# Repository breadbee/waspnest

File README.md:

# Waspnest

This might be something for makefaire tokyo 2020..

```
     ------   -------                                                                         -------
    | RJ45 | | usb-c |                                                                       | usb-c |
     ------   -------                                                                         -------
       |         |                                                                               |
       |    ----------                                                                        --------
       |   | upstream |                                                                      | IP2721 | 
       |   |          |                                                                       --------
       |   |  USB2517 |
       |   |          |   --------
       |   |    port1 |--| ch340e |-----\
       |   |          |   --------      |
       |   |    port2 |--| ch340e |-----|---------\
       |   |          |   --------      |         |
       |   |    port3 |--| ch340e |-----|---------|---------\
       |   |          |   --------      |         |         |
       |   |    port4 |--| ch340e |-----|---------|---------|---------\
       |   |          |   --------      |         |         |         |
       |   |    port5 |--| ch340e |-----|---------|---------|---------|---------\
       |   |          |   --------      |         |         |         |         |
       |   |    port6 |--| ch340e |-----|---------|---------|---------|---------|---------\
       |   |          |   --------      |         |         |         |         |         |
       |   |    port7 |--| ch340e |-----|---------|---------|---------|---------|---------|----------\
       |    ---------     --------      |         |         |         |         |         |          |
       |                                |         |         |         |         |         |          |                      
  ------------                          |         |         |         |         |         |          |
 |   port 0   |                         |         |         |         |         |         |          |
 |            |                         |         |         |         |         |         |          |
 |  RTL8309N  |                         |         |         |         |         |         |          |
 |            |                     ---------     |         |         |         |         |          |
 |      port1 |--------------------| drone 1 |    |         |         |         |         |          |
 |            |                     --------- ---------     |         |         |         |          |
 |      port2 |------------------------------| drone 2 |    |         |         |         |          |
 |            |                               --------- ---------     |         |         |          |
 |      port3 |----------------------------------------| drone 3 |    |         |         |          |
 |            |                                         --------- ---------     |         |          |
 |      port4 |--------------------------------------------------| drone 4 |    |         |          |
 |            |                                                   --------- ---------     |          |
 |      port5 |------------------------------------------------------------| drone 5 |    |          |
 |            |                                                             --------- ---------      |
 |      port6 |----------------------------------------------------------------------| drone 6 |     |
 |            |                                                                       --------- ------------
 |      port7 |--------------------------------------------------------------------------------| Supervisor |
  ------------                                                                                  ------------

```

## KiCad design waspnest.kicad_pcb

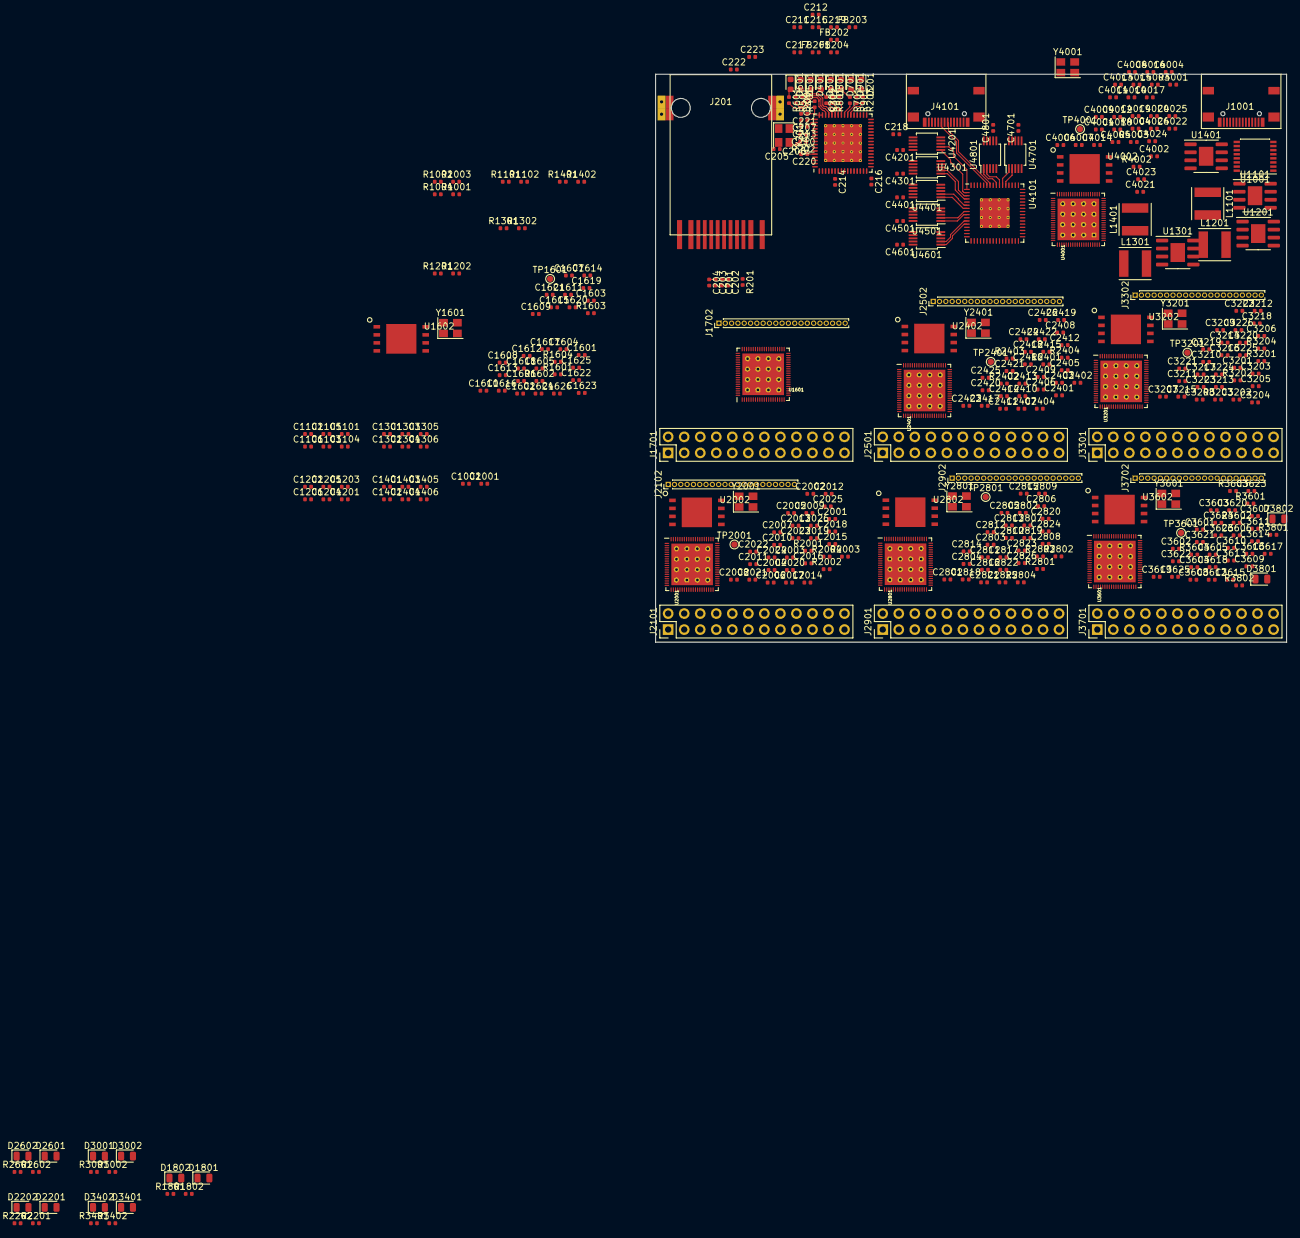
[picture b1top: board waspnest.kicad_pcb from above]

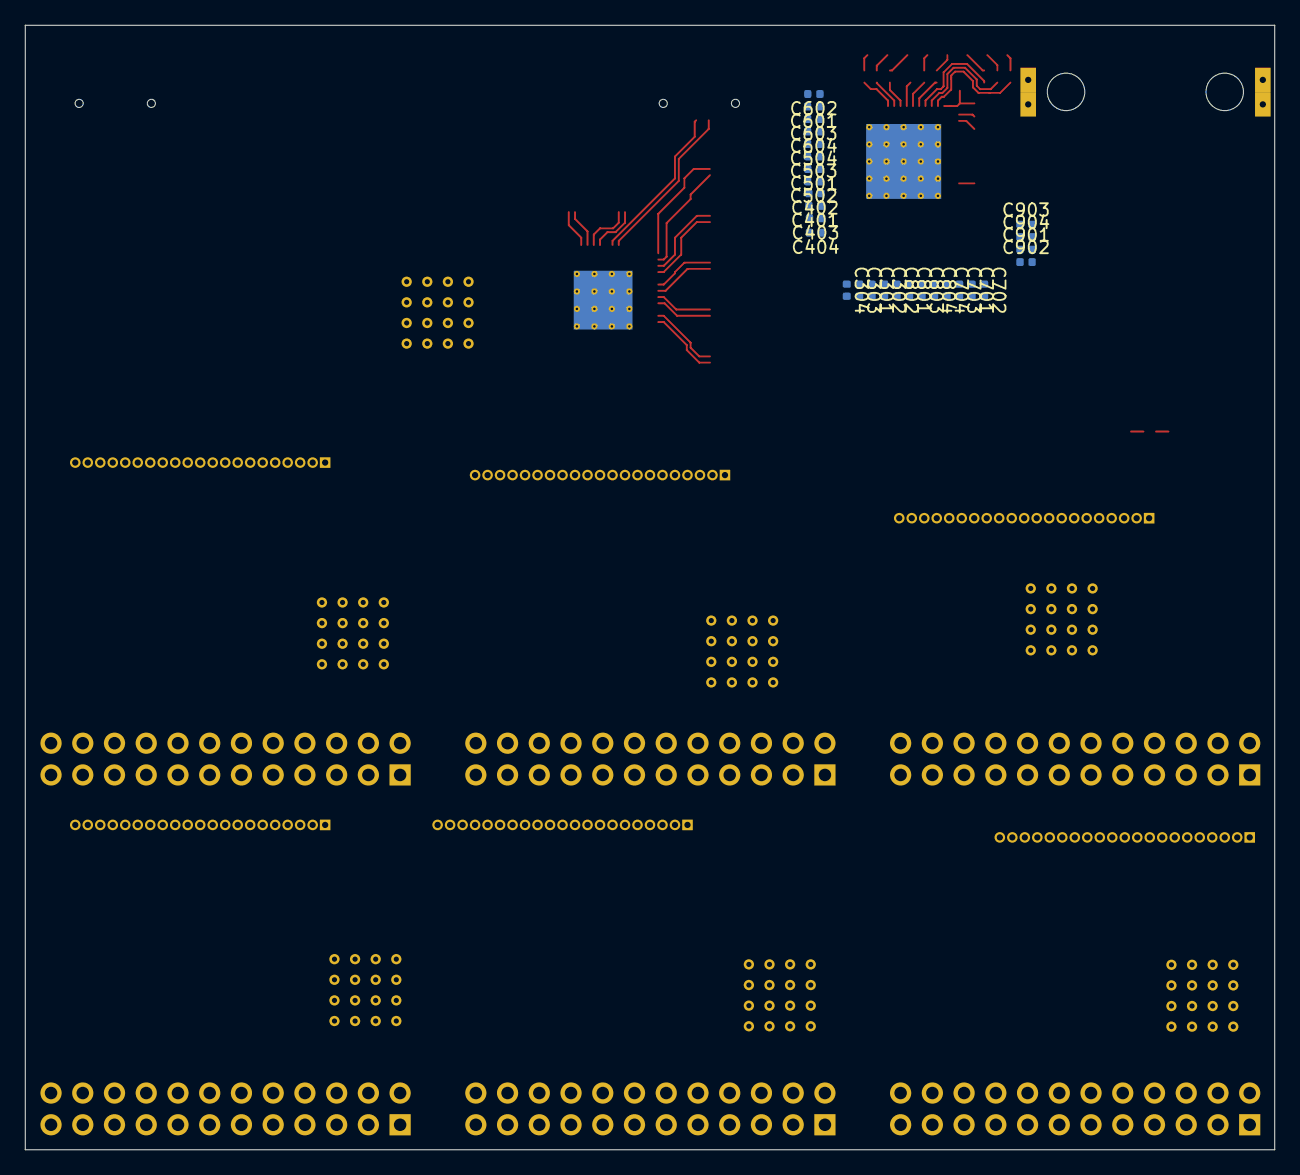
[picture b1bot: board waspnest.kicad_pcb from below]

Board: 4 copper layers, 100.0 x 90.0 mm, 414 parts (28 on the bottom side), 473 nets.

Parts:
C201, C202, C203, C204, C205, C206, C207, C208, C209, C210, C211, C212, C213, C214, C215, C216, C217, C218, C219, C220, C221, C222, C223, C301, C302, C303, C304, C401, C402, C403, C404, C501, C502, C503, C504, C601, C602, C603, C604, C701, C702, C703, C704, C801, C802, C803, C804, C901, C902, C903, C904, C1001, C1002, C1101, C1102, C1103, C1104, C1105, C1106, C1201, C1202, C1203, C1204, C1205, C1206, C1301, C1302, C1303, C1304, C1305, C1306, C1401, C1402, C1403, C1404, C1405, C1406: C; C_0402_1005Metric
C1601, C1602, C1603, C1604, C1605, C1606, C1607, C1608, C1609, C1610, C1611, C1612, C1613, C1614, C1618, C1619, C1621, C1622, C1624, C1626, C2001, C2002, C2003, C2004, C2005, C2006, C2007, C2008, C2009, C2010, C2011, C2012, C2013, C2014, C2018, C2019, C2021, C2022, C2024, C2026, C2401, C2402, C2403, C2404, C2405, C2406, C2407, C2408, C2409, C2410, C2411, C2412, C2413, C2414, C2418, C2419, C2421, C2422, C2424, C2426, C2801, C2802, C2803, C2804, C2805, C2806, C2807, C2808, C2809, C2810, C2811, C2812, C2813, C2814, C2818, C2819, C2821, C2822, C2824, C2826, C3201, C3202, C3203, C3204, C3205, C3206, C3207, C3208, C3209, C3210, C3211, C3212, C3213, C3214, C3218, C3219, C3221, C3222, C3224, C3226, C3601, C3602, C3603, C3604, C3605, C3606, C3607, C3608, C3609, C3610, C3611, C3612, C3613, C3614, C3618, C3619, C3621, C3622, C3624, C3626, C4001, C4002, C4003, C4004, C4005, C4006, C4007, C4008, C4009, C4010, C4011, C4012, C4013, C4014, C4018, C4019, C4021, C4022, C4024, C4026, C4201, C4301, C4401, C4501, C4601, C4701, C4801: 1uf; C_0402_1005Metric
C1615, C1616, C1617, C2015, C2016, C2017, C2415, C2416, C2417, C2815, C2816, C2817, C3215, C3216, C3217, C3615, C3616, C3617, C4015, C4016, C4017: 10uf; C_0402_1005Metric
C1620, C2020, C2420, C2820, C3220, C3620, C4020: 1uF; C_0402_1005Metric
C1623, C1625, C2023, C2025, C2423, C2425, C2823, C2825, C3223, C3225, C3623, C3625, C4023, C4025: 18pf; C_0402_1005Metric
D201, D301, D401, D501, D601, D701, D801, D901: LED; LED_0603_1608Metric
D1801, D1802, D2201, D2202, D2601, D2602, D3001, D3002, D3401, D3402, D3801, D3802: LED_Small; LED_0805_2012Metric
FB201, FB202, FB203, FB204: Ferrite_Bead; L_0402_1005Metric
J201: HR961160C
J1001, J4101: usbc-16p; usbc16p
J1701, J2101, J2501, J2901, J3301, J3701: Conn_02x12_Odd_Even; PinHeader_2x12_P2.54mm_Vertical
J1702, J2102, J2502, J2902, J3302, J3702: Conn_01x21; PinHeader_1x21_P1.00mm_Vertical
L1101, L1201, L1301, L1401: L; L_Taiyo-Yuden_NR-50xx
R201, R203, R301, R401, R501, R601, R701, R801, R901, R1002, R1003, R1004, R1101, R1102, R1201, R1202, R1301, R1302, R1401, R1402: R; R_0402_1005Metric
R202: 2.49K 1%; R_0402_1005Metric
R1001: 100k; R_0402_1005Metric
R1601, R1602, R2001, R2002, R2401, R2402, R2801, R2802, R3201, R3202, R3601, R3602, R4001, R4002: 0; R_0402_1005Metric
R1603, R2003, R2403, R2803, R3203, R3603, R4003: 1.2m; R_0402_1005Metric
R1604, R2004, R2404, R2804, R3204, R3604, R4004: 1m; R_0402_1005Metric
R1801, R1802, R2201, R2202, R2601, R2602, R3001, R3002, R3401, R3402, R3801, R3802: 390; R_0402_1005Metric
TP1601, TP2001, TP2401, TP2801, TP3201, TP3601, TP4001: TestPoint; TestPoint_Pad_D1.0mm
U201: RTL8309N; QFN-64-1EP_9x9mm_P0.5mm_EP6x6mm_ThermalVias
U1001: IP2721; SSOP-16_4.4x5.2mm_P0.65mm
U1101, U1201, U1301, U1401: SY8205FCC; SOIC-8-1EP_3.9x4.9mm_P1.27mm_EP2.29x3mm
U1601, U2001, U2401, U2801, U3201, U3601, U4001: msc313e; QFN-80_EP_8x8_Pitch0.35mm
U1602, U2002, U2402, U2802, U3202, U3602, U4002: spinor; wson8-8x6mm
U4101: USB2517; QFN-64-1EP_9x9mm_P0.5mm_EP4.7x4.7mm_ThermalVias
U4201, U4301, U4401, U4501, U4601, U4701, U4801: ch340e; MSOP-10_3x3mm_P0.5mm
Y201: 25MHz; Crystal_SMD_Abracon_ABM8G-4Pin_3.2x2.5mm
Y1601, Y2001, Y2401, Y2801, Y3201, Y3601, Y4001: Crystal_GND24; Crystal_SMD_Abracon_ABM8G-4Pin_3.2x2.5mm

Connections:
+1V0: C1405.1, C1406.1, C1603.1, C1605.1, C1606.1, C1607.1, C1608.1, C1610.1, C2003.1, C2005.1, C2006.1, C2007.1, C2008.1, C2010.1, C2403.1, C2405.1, C2406.1, C2407.1, C2408.1, C2410.1, C2803.1, C2805.1, C2806.1, C2807.1, C2808.1, C2810.1, C3203.1, C3205.1, C3206.1, C3207.1, C3208.1, C3210.1, C3603.1, C3605.1, C3606.1, C3607.1, C3608.1, C3610.1, C4003.1, C4005.1, C4006.1, C4007.1, C4008.1, C4010.1, L1401.2, R1402.1, U1601.5, U1601.8, U1601.40, U1601.60, U1601.61, U1601.67, U2001.5, U2001.8, U2001.40, U2001.60, U2001.61, U2001.67, U2401.5, U2401.8, U2401.40, U2401.60, U2401.61, U2401.67, U2801.5, U2801.8, U2801.40, U2801.60, U2801.61, U2801.67, U3201.5, U3201.8, U3201.40, U3201.60, U3201.61, U3201.67, U3601.5, U3601.8, U3601.40, U3601.60, U3601.61, U3601.67, U4001.5, U4001.8, U4001.40, U4001.60, U4001.61, U4001.67
+1V8: C1305.1, C1306.1, C1611.1, C1612.1, C1613.1, C2011.1, C2012.1, C2013.1, C2411.1, C2412.1, C2413.1, C2811.1, C2812.1, C2813.1, C3211.1, C3212.1, C3213.1, C3611.1, C3612.1, C3613.1, C4011.1, C4012.1, C4013.1, L1301.2, R1302.1, U1601.3, U1601.4, U1601.6, U2001.3, U2001.4, U2001.6, U2401.3, U2401.4, U2401.6, U2801.3, U2801.4, U2801.6, U3201.3, U3201.4, U3201.6, U3601.3, U3601.4, U3601.6, U4001.3, U4001.4, U4001.6
+3V3: C207.1, C209.1, C1205.1, C1206.1, C1609.1, C1618.1, C1619.1, C1620.1, C1621.1, C1622.1, C1624.1, C1626.1, C2009.1, C2018.1, C2019.1, C2020.1, C2021.1, C2022.1, C2024.1, C2026.1, C2409.1, C2418.1, C2419.1, C2420.1, C2421.1, C2422.1, C2424.1, C2426.1, C2809.1, C2818.1, C2819.1, C2820.1, C2821.1, C2822.1, C2824.1, C2826.1, C3209.1, C3218.1, C3219.1, C3220.1, C3221.1, C3222.1, C3224.1, C3226.1, C3609.1, C3618.1, C3619.1, C3620.1, C3621.1, C3622.1, C3624.1, C3626.1, C4009.1, C4018.1, C4019.1, C4020.1, C4021.1, C4022.1, C4024.1, C4026.1, C4201.1, C4301.1, C4401.1, C4501.1, C4601.1, C4701.1, C4801.1, FB203.2, FB204.2, J1701.2, J1702.1, J2101.2, J2102.1, J2501.2, J2502.1, J2901.2, J2902.1, J3301.2, J3302.1, J3701.2, J3702.1, L1201.2, R1202.1, R1601.1, R1602.1, R2001.1, R2002.1, R2401.1, R2402.1, R2801.1, R2802.1, R3201.1, R3202.1, R3601.1, R3602.1, R4001.1, R4002.1, U201.41, U201.49, U1601.7, U1601.14, U1601.27, U1601.35, U1601.43, U1601.62, U1602.7, U1602.8, U2001.7, U2001.14, U2001.27, U2001.35, U2001.43, U2001.62, U2002.7, U2002.8, U2401.7, U2401.14, U2401.27, U2401.35, U2401.43, U2401.62, U2402.7, U2402.8, U2801.7, U2801.14, U2801.27, U2801.35, U2801.43, U2801.62, U2802.7, U2802.8, U3201.7, U3201.14, U3201.27, U3201.35, U3201.43, U3201.62, U3202.7, U3202.8, U3601.7, U3601.14, U3601.27, U3601.35, U3601.43, U3601.62, U3602.7, U3602.8, U4001.7, U4001.14, U4001.27, U4001.35, U4001.43, U4001.62, U4002.7, U4002.8, U4201.7, U4201.10, U4301.7, U4301.10, U4401.7, U4401.10, U4501.7, U4501.10, U4601.7, U4601.10, U4701.7, U4701.10, U4801.7, U4801.10
+5V: C1105.1, C1106.1, C1614.1, C1615.1, C1616.1, C1617.1, C2014.1, C2015.1, C2016.1, C2017.1, C2414.1, C2415.1, C2416.1, C2417.1, C2814.1, C2815.1, C2816.1, C2817.1, C3214.1, C3215.1, C3216.1, C3217.1, C3614.1, C3615.1, C3616.1, C3617.1, C4014.1, C4015.1, C4016.1, C4017.1, J1701.1, J1702.10, J2101.1, J2102.10, J2501.1, J2502.10, J2901.1, J2902.10, J3301.1, J3302.10, J3701.1, J3702.10, L1101.2, R1102.1
+12V: C1002.1, C1103.2, C1203.2, C1303.2, C1403.2, J1001.a4, J1001.a9, J1001.b4, J1001.b9, R1001.1, U1001.2, U1001.16, U1101.7, U1101.8, U1201.7, U1201.8, U1301.7, U1301.8, U1401.7, U1401.8
/consoles/console_drone0/usb_dn: U4101.3, U4301.2
/consoles/console_drone0/usb_dp: U4101.4, U4301.1
/consoles/console_drone1/usb_dn: U4101.6, U4401.2
/consoles/console_drone1/usb_dp: U4101.7, U4401.1
/consoles/console_drone2/usb_dn: U4101.8, U4501.2
/consoles/console_drone2/usb_dp: U4101.9, U4501.1
/consoles/console_drone3/usb_dn: U4101.11, U4601.2
/consoles/console_drone3/usb_dp: U4101.12, U4601.1
/consoles/console_drone4/usb_dn: U4101.53, U4701.2
/consoles/console_drone4/usb_dp: U4101.54, U4701.1
/consoles/console_drone5/usb_dn: U4101.55, U4801.2
/consoles/console_drone5/usb_dp: U4101.56, U4801.1
/consoles/console_queen/usb_dn: U4101.1, U4201.2
/consoles/console_queen/usb_dp: U4101.2, U4201.1
/drone0/drone_core/fuart_cts: J1701.17, U1601.38
/drone0/drone_core/fuart_rts: J1701.18, U1601.39
/drone0/drone_core/fuart_rx: J1701.15, U1601.36
/drone0/drone_core/fuart_tx: J1701.16, U1601.37
/drone0/drone_core/i2c1_scl: J1701.5, U1601.41
/drone0/drone_core/i2c1_sda: J1701.6, U1601.42
/drone0/drone_core/pm_gpio4: J1701.4, U1601.21
/drone0/drone_core/pm_sd_cdz: J1702.8, U1601.15
/drone0/drone_core/reset: C1609.2, R1603.1, U1601.17
/drone0/drone_core/sar_gpio0: J1701.14, U1601.12
/drone0/drone_core/sar_gpio1: J1701.13, U1601.11
/drone0/drone_core/sar_gpio2: J1701.11, U1601.10
/drone0/drone_core/sar_gpio3: J1701.12, U1601.9
/drone0/drone_core/sd_clk: J1702.7, U1601.68
/drone0/drone_core/sd_cmd: J1702.6, U1601.69
/drone0/drone_core/sd_d0: J1702.5, U1601.70
/drone0/drone_core/sd_d1: J1702.4, U1601.71
/drone0/drone_core/sd_d2: J1702.3, U1601.72
/drone0/drone_core/sd_d3: J1702.2, U1601.73
/drone0/drone_core/spi0_ck: J1701.8, U1601.64
/drone0/drone_core/spi0_cz: J1701.7, U1601.63
/drone0/drone_core/spi0_di: J1701.9, U1601.65
/drone0/drone_core/spi0_do: J1701.10, U1601.66
/drone0/drone_core/spinor_miso: U1601.25, U1602.2
/drone0/drone_core/spinor_mosi: U1601.23, U1602.5
/drone0/drone_core/spinor_sck: U1601.26, U1602.6
/drone0/drone_core/spinor_~cs: U1601.22, U1602.1
/drone0/drone_core/spinor_~wp: U1601.24, U1602.3
/drone0/drone_core/sr_io2: J1701.24, U1601.44
/drone0/drone_core/sr_io3: J1701.23, U1601.45
/drone0/drone_core/sr_io4: J1701.22, U1601.46
/drone0/drone_core/sr_io5: J1701.21, U1601.47
/drone0/drone_core/sr_io6: J1701.20, U1601.48
/drone0/drone_core/sr_io7: J1701.19, U1601.49
/drone0/drone_core/sr_io8: J1702.21, U1601.50
/drone0/drone_core/sr_io9: J1702.20, U1601.51
/drone0/drone_core/sr_io10: J1702.19, U1601.52
/drone0/drone_core/sr_io11: J1702.18, U1601.53
/drone0/drone_core/sr_io12: J1702.17, U1601.54
/drone0/drone_core/sr_io13: J1702.16, U1601.55
/drone0/drone_core/sr_io14: J1702.15, U1601.56
/drone0/drone_core/sr_io15: J1702.14, U1601.57
/drone0/drone_core/usb_dm: J1702.11, U1601.75
/drone0/drone_core/usb_dp: J1702.12, U1601.76
/drone0/drone_core/xtal_in: C1623.1, R1604.2, U1601.28, Y1601.1
/drone0/drone_core/xtal_out: C1625.1, R1604.1, U1601.29, Y1601.3
/drone0/drone_leds/led0: R1801.1, U1601.58
/drone0/drone_leds/led1: R1802.1, U1601.59
/drone1/drone_core/fuart_cts: J2101.17, U2001.38
/drone1/drone_core/fuart_rts: J2101.18, U2001.39
/drone1/drone_core/fuart_rx: J2101.15, U2001.36
/drone1/drone_core/fuart_tx: J2101.16, U2001.37
/drone1/drone_core/i2c1_scl: J2101.5, U2001.41
/drone1/drone_core/i2c1_sda: J2101.6, U2001.42
/drone1/drone_core/pm_gpio4: J2101.4, U2001.21
/drone1/drone_core/pm_sd_cdz: J2102.8, U2001.15
/drone1/drone_core/reset: C2009.2, R2003.1, U2001.17
/drone1/drone_core/sar_gpio0: J2101.14, U2001.12
/drone1/drone_core/sar_gpio1: J2101.13, U2001.11
/drone1/drone_core/sar_gpio2: J2101.11, U2001.10
/drone1/drone_core/sar_gpio3: J2101.12, U2001.9
/drone1/drone_core/sd_clk: J2102.7, U2001.68
/drone1/drone_core/sd_cmd: J2102.6, U2001.69
/drone1/drone_core/sd_d0: J2102.5, U2001.70
/drone1/drone_core/sd_d1: J2102.4, U2001.71
/drone1/drone_core/sd_d2: J2102.3, U2001.72
/drone1/drone_core/sd_d3: J2102.2, U2001.73
/drone1/drone_core/spi0_ck: J2101.8, U2001.64
/drone1/drone_core/spi0_cz: J2101.7, U2001.63
/drone1/drone_core/spi0_di: J2101.9, U2001.65
/drone1/drone_core/spi0_do: J2101.10, U2001.66
/drone1/drone_core/spinor_miso: U2001.25, U2002.2
/drone1/drone_core/spinor_mosi: U2001.23, U2002.5
/drone1/drone_core/spinor_sck: U2001.26, U2002.6
/drone1/drone_core/spinor_~cs: U2001.22, U2002.1
/drone1/drone_core/spinor_~wp: U2001.24, U2002.3
/drone1/drone_core/sr_io2: J2101.24, U2001.44
/drone1/drone_core/sr_io3: J2101.23, U2001.45
/drone1/drone_core/sr_io4: J2101.22, U2001.46
/drone1/drone_core/sr_io5: J2101.21, U2001.47
/drone1/drone_core/sr_io6: J2101.20, U2001.48
/drone1/drone_core/sr_io7: J2101.19, U2001.49
/drone1/drone_core/sr_io8: J2102.21, U2001.50
/drone1/drone_core/sr_io9: J2102.20, U2001.51
/drone1/drone_core/sr_io10: J2102.19, U2001.52
/drone1/drone_core/sr_io11: J2102.18, U2001.53
/drone1/drone_core/sr_io12: J2102.17, U2001.54
/drone1/drone_core/sr_io13: J2102.16, U2001.55
/drone1/drone_core/sr_io14: J2102.15, U2001.56
/drone1/drone_core/sr_io15: J2102.14, U2001.57
/drone1/drone_core/usb_dm: J2102.11, U2001.75
/drone1/drone_core/usb_dp: J2102.12, U2001.76
/drone1/drone_core/xtal_in: C2023.1, R2004.2, U2001.28, Y2001.1
/drone1/drone_core/xtal_out: C2025.1, R2004.1, U2001.29, Y2001.3
/drone1/drone_leds/led0: R2201.1, U2001.58
/drone1/drone_leds/led1: R2202.1, U2001.59
/drone2/drone_core/fuart_cts: J2501.17, U2401.38
/drone2/drone_core/fuart_rts: J2501.18, U2401.39
/drone2/drone_core/fuart_rx: J2501.15, U2401.36
/drone2/drone_core/fuart_tx: J2501.16, U2401.37
/drone2/drone_core/i2c1_scl: J2501.5, U2401.41
/drone2/drone_core/i2c1_sda: J2501.6, U2401.42
/drone2/drone_core/pm_gpio4: J2501.4, U2401.21
/drone2/drone_core/pm_sd_cdz: J2502.8, U2401.15
/drone2/drone_core/reset: C2409.2, R2403.1, U2401.17
/drone2/drone_core/sar_gpio0: J2501.14, U2401.12
/drone2/drone_core/sar_gpio1: J2501.13, U2401.11
/drone2/drone_core/sar_gpio2: J2501.11, U2401.10
/drone2/drone_core/sar_gpio3: J2501.12, U2401.9
/drone2/drone_core/sd_clk: J2502.7, U2401.68
/drone2/drone_core/sd_cmd: J2502.6, U2401.69
/drone2/drone_core/sd_d0: J2502.5, U2401.70
/drone2/drone_core/sd_d1: J2502.4, U2401.71
/drone2/drone_core/sd_d2: J2502.3, U2401.72
/drone2/drone_core/sd_d3: J2502.2, U2401.73
/drone2/drone_core/spi0_ck: J2501.8, U2401.64
/drone2/drone_core/spi0_cz: J2501.7, U2401.63
/drone2/drone_core/spi0_di: J2501.9, U2401.65
/drone2/drone_core/spi0_do: J2501.10, U2401.66
/drone2/drone_core/spinor_miso: U2401.25, U2402.2
/drone2/drone_core/spinor_mosi: U2401.23, U2402.5
/drone2/drone_core/spinor_sck: U2401.26, U2402.6
/drone2/drone_core/spinor_~cs: U2401.22, U2402.1
/drone2/drone_core/spinor_~wp: U2401.24, U2402.3
/drone2/drone_core/sr_io2: J2501.24, U2401.44
/drone2/drone_core/sr_io3: J2501.23, U2401.45
/drone2/drone_core/sr_io4: J2501.22, U2401.46
/drone2/drone_core/sr_io5: J2501.21, U2401.47
/drone2/drone_core/sr_io6: J2501.20, U2401.48
/drone2/drone_core/sr_io7: J2501.19, U2401.49
/drone2/drone_core/sr_io8: J2502.21, U2401.50
/drone2/drone_core/sr_io9: J2502.20, U2401.51
/drone2/drone_core/sr_io10: J2502.19, U2401.52
/drone2/drone_core/sr_io11: J2502.18, U2401.53
/drone2/drone_core/sr_io12: J2502.17, U2401.54
/drone2/drone_core/sr_io13: J2502.16, U2401.55
/drone2/drone_core/sr_io14: J2502.15, U2401.56
/drone2/drone_core/sr_io15: J2502.14, U2401.57
/drone2/drone_core/usb_dm: J2502.11, U2401.75
/drone2/drone_core/usb_dp: J2502.12, U2401.76
/drone2/drone_core/xtal_in: C2423.1, R2404.2, U2401.28, Y2401.1
/drone2/drone_core/xtal_out: C2425.1, R2404.1, U2401.29, Y2401.3
/drone2/drone_leds/led0: R2601.1, U2401.58
/drone2/drone_leds/led1: R2602.1, U2401.59
/drone3/drone_core/fuart_cts: J2901.17, U2801.38
/drone3/drone_core/fuart_rts: J2901.18, U2801.39
/drone3/drone_core/fuart_rx: J2901.15, U2801.36
/drone3/drone_core/fuart_tx: J2901.16, U2801.37
/drone3/drone_core/i2c1_scl: J2901.5, U2801.41
/drone3/drone_core/i2c1_sda: J2901.6, U2801.42
/drone3/drone_core/pm_gpio4: J2901.4, U2801.21
/drone3/drone_core/pm_sd_cdz: J2902.8, U2801.15
/drone3/drone_core/reset: C2809.2, R2803.1, U2801.17
/drone3/drone_core/sar_gpio0: J2901.14, U2801.12
/drone3/drone_core/sar_gpio1: J2901.13, U2801.11
/drone3/drone_core/sar_gpio2: J2901.11, U2801.10
/drone3/drone_core/sar_gpio3: J2901.12, U2801.9
/drone3/drone_core/sd_clk: J2902.7, U2801.68
/drone3/drone_core/sd_cmd: J2902.6, U2801.69
/drone3/drone_core/sd_d0: J2902.5, U2801.70
/drone3/drone_core/sd_d1: J2902.4, U2801.71
/drone3/drone_core/sd_d2: J2902.3, U2801.72
/drone3/drone_core/sd_d3: J2902.2, U2801.73
/drone3/drone_core/spi0_ck: J2901.8, U2801.64
/drone3/drone_core/spi0_cz: J2901.7, U2801.63
/drone3/drone_core/spi0_di: J2901.9, U2801.65
/drone3/drone_core/spi0_do: J2901.10, U2801.66
/drone3/drone_core/spinor_miso: U2801.25, U2802.2
/drone3/drone_core/spinor_mosi: U2801.23, U2802.5
/drone3/drone_core/spinor_sck: U2801.26, U2802.6
/drone3/drone_core/spinor_~cs: U2801.22, U2802.1
/drone3/drone_core/spinor_~wp: U2801.24, U2802.3
/drone3/drone_core/sr_io2: J2901.24, U2801.44
/drone3/drone_core/sr_io3: J2901.23, U2801.45
/drone3/drone_core/sr_io4: J2901.22, U2801.46
/drone3/drone_core/sr_io5: J2901.21, U2801.47
/drone3/drone_core/sr_io6: J2901.20, U2801.48
/drone3/drone_core/sr_io7: J2901.19, U2801.49
/drone3/drone_core/sr_io8: J2902.21, U2801.50
/drone3/drone_core/sr_io9: J2902.20, U2801.51
/drone3/drone_core/sr_io10: J2902.19, U2801.52
/drone3/drone_core/sr_io11: J2902.18, U2801.53
/drone3/drone_core/sr_io12: J2902.17, U2801.54
/drone3/drone_core/sr_io13: J2902.16, U2801.55
/drone3/drone_core/sr_io14: J2902.15, U2801.56
/drone3/drone_core/sr_io15: J2902.14, U2801.57
/drone3/drone_core/usb_dm: J2902.11, U2801.75
/drone3/drone_core/usb_dp: J2902.12, U2801.76
/drone3/drone_core/xtal_in: C2823.1, R2804.2, U2801.28, Y2801.1
/drone3/drone_core/xtal_out: C2825.1, R2804.1, U2801.29, Y2801.3
/drone3/drone_leds/led0: R3001.1, U2801.58
/drone3/drone_leds/led1: R3002.1, U2801.59
/drone4/drone_core/fuart_cts: J3301.17, U3201.38
/drone4/drone_core/fuart_rts: J3301.18, U3201.39
/drone4/drone_core/fuart_rx: J3301.15, U3201.36
/drone4/drone_core/fuart_tx: J3301.16, U3201.37
/drone4/drone_core/i2c1_scl: J3301.5, U3201.41
/drone4/drone_core/i2c1_sda: J3301.6, U3201.42
/drone4/drone_core/pm_gpio4: J3301.4, U3201.21
/drone4/drone_core/pm_sd_cdz: J3302.8, U3201.15
/drone4/drone_core/reset: C3209.2, R3203.1, U3201.17
/drone4/drone_core/sar_gpio0: J3301.14, U3201.12
/drone4/drone_core/sar_gpio1: J3301.13, U3201.11
/drone4/drone_core/sar_gpio2: J3301.11, U3201.10
/drone4/drone_core/sar_gpio3: J3301.12, U3201.9
/drone4/drone_core/sd_clk: J3302.7, U3201.68
/drone4/drone_core/sd_cmd: J3302.6, U3201.69
/drone4/drone_core/sd_d0: J3302.5, U3201.70
/drone4/drone_core/sd_d1: J3302.4, U3201.71
/drone4/drone_core/sd_d2: J3302.3, U3201.72
/drone4/drone_core/sd_d3: J3302.2, U3201.73
/drone4/drone_core/spi0_ck: J3301.8, U3201.64
/drone4/drone_core/spi0_cz: J3301.7, U3201.63
/drone4/drone_core/spi0_di: J3301.9, U3201.65
/drone4/drone_core/spi0_do: J3301.10, U3201.66
/drone4/drone_core/spinor_miso: U3201.25, U3202.2
/drone4/drone_core/spinor_mosi: U3201.23, U3202.5
/drone4/drone_core/spinor_sck: U3201.26, U3202.6
/drone4/drone_core/spinor_~cs: U3201.22, U3202.1
/drone4/drone_core/spinor_~wp: U3201.24, U3202.3
/drone4/drone_core/sr_io2: J3301.24, U3201.44
/drone4/drone_core/sr_io3: J3301.23, U3201.45
/drone4/drone_core/sr_io4: J3301.22, U3201.46
/drone4/drone_core/sr_io5: J3301.21, U3201.47
/drone4/drone_core/sr_io6: J3301.20, U3201.48
/drone4/drone_core/sr_io7: J3301.19, U3201.49
/drone4/drone_core/sr_io8: J3302.21, U3201.50
/drone4/drone_core/sr_io9: J3302.20, U3201.51
/drone4/drone_core/sr_io10: J3302.19, U3201.52
/drone4/drone_core/sr_io11: J3302.18, U3201.53
/drone4/drone_core/sr_io12: J3302.17, U3201.54
/drone4/drone_core/sr_io13: J3302.16, U3201.55
/drone4/drone_core/sr_io14: J3302.15, U3201.56
/drone4/drone_core/sr_io15: J3302.14, U3201.57
/drone4/drone_core/usb_dm: J3302.11, U3201.75
/drone4/drone_core/usb_dp: J3302.12, U3201.76
/drone4/drone_core/xtal_in: C3223.1, R3204.2, U3201.28, Y3201.1
/drone4/drone_core/xtal_out: C3225.1, R3204.1, U3201.29, Y3201.3
/drone4/drone_leds/led0: R3401.1, U3201.58
/drone4/drone_leds/led1: R3402.1, U3201.59
/drone5/drone_core/fuart_cts: J3701.17, U3601.38
/drone5/drone_core/fuart_rts: J3701.18, U3601.39
/drone5/drone_core/fuart_rx: J3701.15, U3601.36
/drone5/drone_core/fuart_tx: J3701.16, U3601.37
/drone5/drone_core/i2c1_scl: J3701.5, U3601.41
/drone5/drone_core/i2c1_sda: J3701.6, U3601.42
/drone5/drone_core/pm_gpio4: J3701.4, U3601.21
/drone5/drone_core/pm_sd_cdz: J3702.8, U3601.15
/drone5/drone_core/reset: C3609.2, R3603.1, U3601.17
/drone5/drone_core/sar_gpio0: J3701.14, U3601.12
/drone5/drone_core/sar_gpio1: J3701.13, U3601.11
/drone5/drone_core/sar_gpio2: J3701.11, U3601.10
/drone5/drone_core/sar_gpio3: J3701.12, U3601.9
/drone5/drone_core/sd_clk: J3702.7, U3601.68
/drone5/drone_core/sd_cmd: J3702.6, U3601.69
/drone5/drone_core/sd_d0: J3702.5, U3601.70
/drone5/drone_core/sd_d1: J3702.4, U3601.71
/drone5/drone_core/sd_d2: J3702.3, U3601.72
/drone5/drone_core/sd_d3: J3702.2, U3601.73
/drone5/drone_core/spi0_ck: J3701.8, U3601.64
/drone5/drone_core/spi0_cz: J3701.7, U3601.63
/drone5/drone_core/spi0_di: J3701.9, U3601.65
/drone5/drone_core/spi0_do: J3701.10, U3601.66
/drone5/drone_core/spinor_miso: U3601.25, U3602.2
/drone5/drone_core/spinor_mosi: U3601.23, U3602.5
/drone5/drone_core/spinor_sck: U3601.26, U3602.6
/drone5/drone_core/spinor_~cs: U3601.22, U3602.1
/drone5/drone_core/spinor_~wp: U3601.24, U3602.3
/drone5/drone_core/sr_io2: J3701.24, U3601.44
/drone5/drone_core/sr_io3: J3701.23, U3601.45
/drone5/drone_core/sr_io4: J3701.22, U3601.46
/drone5/drone_core/sr_io5: J3701.21, U3601.47
/drone5/drone_core/sr_io6: J3701.20, U3601.48
/drone5/drone_core/sr_io7: J3701.19, U3601.49
/drone5/drone_core/sr_io8: J3702.21, U3601.50
/drone5/drone_core/sr_io9: J3702.20, U3601.51
/drone5/drone_core/sr_io10: J3702.19, U3601.52
/drone5/drone_core/sr_io11: J3702.18, U3601.53
/drone5/drone_core/sr_io12: J3702.17, U3601.54
/drone5/drone_core/sr_io13: J3702.16, U3601.55
/drone5/drone_core/sr_io14: J3702.15, U3601.56
/drone5/drone_core/sr_io15: J3702.14, U3601.57
/drone5/drone_core/usb_dm: J3702.11, U3601.75
/drone5/drone_core/usb_dp: J3702.12, U3601.76
/drone5/drone_core/xtal_in: C3623.1, R3604.2, U3601.28, Y3601.1
/drone5/drone_core/xtal_out: C3625.1, R3604.1, U3601.29, Y3601.3
/drone5/drone_leds/led0: R3801.1, U3601.58
/drone5/drone_leds/led1: R3802.1, U3601.59
/queen/console_rx: U4001.19, U4201.8
/queen/console_tx: U4001.18, U4201.9
/queen/core/reset: C4009.2, R4003.1, U4001.17
/queen/core/spinor_miso: U4001.25, U4002.2
/queen/core/spinor_mosi: U4001.23, U4002.5
/queen/core/spinor_sck: U4001.26, U4002.6
/queen/core/spinor_~cs: U4001.22, U4002.1
/queen/core/spinor_~wp: U4001.24, U4002.3
/queen/core/xtal_in: C4023.1, R4004.2, U4001.28, Y4001.1
/queen/core/xtal_out: C4025.1, R4004.1, U4001.29, Y4001.3
/queen/ethernet_rxn: C903.1, U4001.31
/queen/ethernet_rxp: C904.1, U4001.32
/queen/ethernet_txn: C901.1, U4001.33
/queen/ethernet_txp: C902.1, U4001.34
/rtlswch/analog_1v0: C211.1, C212.1, C215.1, C217.1, C219.1, FB202.1, U201.1, U201.12, U201.22, U201.32, U201.55
/rtlswch/analog_3v3: C214.1, C216.1, C218.1, C220.1, FB204.1, U201.6, U201.17, U201.27, U201.60
/rtlswch/drone0_rxn: C703.1, U1601.31
/rtlswch/drone0_rxp: C704.1, U1601.32
/rtlswch/drone0_txn: C701.1, U1601.33
/rtlswch/drone0_txp: C702.1, U1601.34
/rtlswch/drone1_rxn: C803.1, U2001.31
/rtlswch/drone1_rxp: C804.1, U2001.32
/rtlswch/drone1_txn: C801.1, U2001.33
/rtlswch/drone1_txp: C802.1, U2001.34
/rtlswch/drone2_rxn: C303.1, U2401.31
/rtlswch/drone2_rxp: C304.1, U2401.32
/rtlswch/drone2_txn: C301.1, U2401.33
/rtlswch/drone2_txp: C302.1, U2401.34
/rtlswch/drone3_rxn: C403.1, U2801.31
/rtlswch/drone3_rxp: C404.1, U2801.32
/rtlswch/drone3_txn: C401.1, U2801.33
/rtlswch/drone3_txp: C402.1, U2801.34
/rtlswch/drone4_rxn: C503.1, U3201.31
/rtlswch/drone4_rxp: C504.1, U3201.32
/rtlswch/drone4_txn: C501.1, U3201.33
/rtlswch/drone4_txp: C502.1, U3201.34
/rtlswch/drone5_rxn: C603.1, U3601.31
/rtlswch/drone5_rxp: C604.1, U3601.32
/rtlswch/drone5_txn: C601.1, U3601.33
/rtlswch/drone5_txp: C602.1, U3601.34
/rtlswch/pll_1v0: C210.1, FB201.1, U201.53
/rtlswch/pll_3v3: C213.1, FB203.1, U201.50
/rtlswch/sw_1v0: C208.1, C221.1, C222.1, C223.1, FB201.2, FB202.2, U201.11, U201.33, U201.47, U201.48
/rtlswch/switch_drone_port2/led: R701.2, U201.40
/rtlswch/switch_drone_port2/switch_rxn: C701.2, U201.3
/rtlswch/switch_drone_port2/switch_rxp: C702.2, U201.2
/rtlswch/switch_drone_port2/switch_txn: C703.2, U201.4
/rtlswch/switch_drone_port2/switch_txp: C704.2, U201.5
/rtlswch/switch_drone_port3/led: R801.2, U201.42
/rtlswch/switch_drone_port3/switch_rxn: C801.2, U201.9
/rtlswch/switch_drone_port3/switch_rxp: C802.2, U201.10
/rtlswch/switch_drone_port3/switch_txn: C803.2, U201.8
/rtlswch/switch_drone_port3/switch_txp: C804.2, U201.7
/rtlswch/switch_drone_port4/led: R301.2, U201.43
/rtlswch/switch_drone_port4/switch_rxn: C301.2, U201.14
/rtlswch/switch_drone_port4/switch_rxp: C302.2, U201.13
/rtlswch/switch_drone_port4/switch_txn: C303.2, U201.15
/rtlswch/switch_drone_port4/switch_txp: C304.2, U201.16
/rtlswch/switch_drone_port5/led: R401.2, U201.44
/rtlswch/switch_drone_port5/switch_rxn: C401.2, U201.20
/rtlswch/switch_drone_port5/switch_rxp: C402.2, U201.21
/rtlswch/switch_drone_port5/switch_txn: C403.2, U201.19
/rtlswch/switch_drone_port5/switch_txp: C404.2, U201.18
/rtlswch/switch_drone_port6/led: R501.2, U201.45
/rtlswch/switch_drone_port6/switch_rxn: C501.2, U201.24
/rtlswch/switch_drone_port6/switch_rxp: C502.2, U201.23
/rtlswch/switch_drone_port6/switch_txn: C503.2, U201.25
/rtlswch/switch_drone_port6/switch_txp: C504.2, U201.26
/rtlswch/switch_drone_port7/led: R601.2, U201.46
/rtlswch/switch_drone_port7/switch_rxn: C601.2, U201.30
/rtlswch/switch_drone_port7/switch_rxp: C602.2, U201.31
/rtlswch/switch_drone_port7/switch_txn: C603.2, U201.29
/rtlswch/switch_drone_port7/switch_txp: C604.2, U201.28
/rtlswch/switch_queen/led: R901.2, U201.39
/rtlswch/switch_queen/switch_rxn: C901.2, U201.63
/rtlswch/switch_queen/switch_rxp: C902.2, U201.64
/rtlswch/switch_queen/switch_txn: C903.2, U201.61
/rtlswch/switch_queen/switch_txp: C904.2, U201.62
/rtlswch/upstream_rxn: J201.8, U201.57
/rtlswch/upstream_rxp: J201.7, U201.56
/rtlswch/upstream_txn: J201.4, U201.59
/rtlswch/upstream_txp: J201.3, U201.58
GND: C201.2, C202.2, C203.2, C204.2, C205.1, C206.2, C207.2, C208.2, C209.2, C210.2, C211.2, C212.2, C213.2, C214.2, C215.2, C216.2, C217.2, C218.2, C219.2, C220.2, C221.2, C222.2, C223.2, C1001.2, C1002.2, C1101.2, C1102.2, C1103.1, C1106.2, C1201.2, C1202.2, C1203.1, C1206.2, C1301.2, C1302.2, C1303.1, C1306.2, C1401.2, C1402.2, C1403.1, C1406.2, C1601.2, C1602.2, C1603.2, C1604.2, C1605.2, C1606.2, C1607.2, C1608.2, C1610.2, C1611.2, C1612.2, C1613.2, C1614.2, C1615.2, C1616.2, C1617.2, C1618.2, C1619.2, C1620.2, C1621.2, C1622.2, C1623.2, C1624.2, C1625.2, C1626.2, C2001.2, C2002.2, C2003.2, C2004.2, C2005.2, C2006.2, C2007.2, C2008.2, C2010.2, C2011.2, C2012.2, C2013.2, C2014.2, C2015.2, C2016.2, C2017.2, C2018.2, C2019.2, C2020.2, C2021.2, C2022.2, C2023.2, C2024.2, C2025.2, C2026.2, C2401.2, C2402.2, C2403.2, C2404.2, C2405.2, C2406.2, C2407.2, C2408.2, C2410.2, C2411.2, C2412.2, C2413.2, C2414.2, C2415.2, C2416.2, C2417.2, C2418.2, C2419.2, C2420.2, C2421.2, C2422.2, C2423.2, C2424.2, C2425.2, C2426.2, C2801.2, C2802.2, C2803.2, C2804.2, C2805.2, C2806.2, C2807.2, C2808.2, C2810.2, C2811.2, C2812.2, C2813.2, C2814.2, C2815.2, C2816.2, C2817.2, C2818.2, C2819.2, C2820.2, C2821.2, C2822.2, C2823.2, C2824.2, C2825.2, C2826.2, C3201.2, C3202.2, C3203.2, C3204.2, C3205.2, C3206.2, C3207.2, C3208.2, C3210.2, C3211.2, C3212.2, C3213.2, C3214.2, C3215.2, C3216.2, C3217.2, C3218.2, C3219.2, C3220.2, C3221.2, C3222.2, C3223.2, C3224.2, C3225.2, C3226.2, C3601.2, C3602.2, C3603.2, C3604.2, C3605.2, C3606.2, C3607.2, C3608.2, C3610.2, C3611.2, C3612.2, C3613.2, C3614.2, C3615.2, C3616.2, C3617.2, C3618.2, C3619.2, C3620.2, C3621.2, C3622.2, C3623.2, C3624.2, C3625.2, C3626.2, C4001.2, C4002.2, C4003.2, C4004.2, C4005.2, C4006.2, C4007.2, C4008.2, C4010.2, C4011.2, C4012.2, C4013.2, C4014.2, C4015.2, C4016.2, C4017.2, C4018.2, C4019.2, C4020.2, C4021.2, C4022.2, C4023.2, C4024.2, C4025.2, C4026.2, C4201.2, C4301.2, C4401.2, C4501.2, C4601.2, C4701.2, C4801.2, D201.1, D301.1, D401.1, D501.1, D601.1, D701.1, D801.1, D901.1, D1801.1, D1802.1, D2201.1, D2202.1, D2601.1, D2602.1, D3001.1, D3002.1, D3401.1, D3402.1, D3801.1, D3802.1, J1001.a1, J1001.a12, J1001.b1, J1001.b12, J1701.3, J1702.9, J1702.13, J2101.3, J2102.9, J2102.13, J2501.3, J2502.9, J2502.13, J2901.3, J2902.9, J2902.13, J3301.3, J3302.9, J3302.13, J3701.3, J3702.9, J3702.13, R201.2, R202.2, R1002.2, R1003.2, R1004.2, R1101.2, R1201.2, R1301.2, R1401.2, U201.65, U1001.5, U1101.9, U1201.9, U1301.9, U1401.9, U1601.20, U1601.81, U1602.4, U2001.20, U2001.81, U2002.4, U2401.20, U2401.81, U2402.4, U2801.20, U2801.81, U2802.4, U3201.20, U3201.81, U3202.4, U3601.20, U3601.81, U3602.4, U4001.20, U4001.81, U4002.4, U4101.65, U4201.3, U4301.3, U4401.3, U4501.3, U4601.3, U4701.3, U4801.3, Y201.2, Y201.4, Y1601.2, Y1601.4, Y2001.2, Y2001.4, Y2401.2, Y2401.4, Y2801.2, Y2801.4, Y3201.2, Y3201.4, Y3601.2, Y3601.4, Y4001.2, Y4001.4
unnamed: C201.1, C202.1, J201.6
unnamed: C203.1, C204.1, J201.5
unnamed: C205.2, U201.51, Y201.1
unnamed: C206.1, U201.52, Y201.3
unnamed: C1001.1, J1001.a5, R1003.1, U1001.13
unnamed: C1101.1, U1101.4
unnamed: C1102.1, U1101.6
unnamed: C1104.1, L1101.1, U1101.2
unnamed: C1104.2, U1101.1
unnamed: C1105.2, R1101.1, R1102.2, U1101.5
unnamed: C1201.1, U1201.4
unnamed: C1202.1, U1201.6
unnamed: C1204.1, L1201.1, U1201.2
unnamed: C1204.2, U1201.1
unnamed: C1205.2, R1201.1, R1202.2, U1201.5
unnamed: C1301.1, U1301.4
unnamed: C1302.1, U1301.6
unnamed: C1304.1, L1301.1, U1301.2
unnamed: C1304.2, U1301.1
unnamed: C1305.2, R1301.1, R1302.2, U1301.5
unnamed: C1401.1, U1401.4
unnamed: C1402.1, U1401.6
unnamed: C1404.1, L1401.1, U1401.2
unnamed: C1404.2, U1401.1
unnamed: C1405.2, R1401.1, R1402.2, U1401.5
unnamed: C1601.1, U1601.13
unnamed: C1602.1, R1601.2, U1601.74
unnamed: C1604.1, R1602.2, U1601.30
unnamed: C2001.1, U2001.13
unnamed: C2002.1, R2001.2, U2001.74
unnamed: C2004.1, R2002.2, U2001.30
unnamed: C2401.1, U2401.13
unnamed: C2402.1, R2401.2, U2401.74
unnamed: C2404.1, R2402.2, U2401.30
unnamed: C2801.1, U2801.13
unnamed: C2802.1, R2801.2, U2801.74
unnamed: C2804.1, R2802.2, U2801.30
unnamed: C3201.1, U3201.13
unnamed: C3202.1, R3201.2, U3201.74
unnamed: C3204.1, R3202.2, U3201.30
unnamed: C3601.1, U3601.13
unnamed: C3602.1, R3601.2, U3601.74
unnamed: C3604.1, R3602.2, U3601.30
unnamed: C4001.1, U4001.13
unnamed: C4002.1, R4001.2, U4001.74
unnamed: C4004.1, R4002.2, U4001.30
unnamed: D201.2, R203.1
unnamed: D301.2, R301.1
unnamed: D401.2, R401.1
unnamed: D501.2, R501.1
unnamed: D601.2, R601.1
unnamed: D701.2, R701.1
unnamed: D801.2, R801.1
unnamed: D901.2, R901.1
unnamed: D1801.2, R1801.2
unnamed: D1802.2, R1802.2
unnamed: D2201.2, R2201.2
unnamed: D2202.2, R2202.2
unnamed: D2601.2, R2601.2
unnamed: D2602.2, R2602.2
unnamed: D3001.2, R3001.2
unnamed: D3002.2, R3002.2
unnamed: D3401.2, R3401.2
unnamed: D3402.2, R3402.2
unnamed: D3801.2, R3801.2
unnamed: D3802.2, R3802.2
unnamed: J201.10, R201.1
unnamed: J1001.b5, R1002.1, U1001.12
unnamed: J1001.shield, R1004.1
unnamed: J4101.a1, J4101.a12, J4101.b1, J4101.b12
unnamed: J4101.a4, J4101.a9, J4101.b4, J4101.b9
unnamed: J4101.a6, J4101.b6, U4101.59
unnamed: J4101.a7, J4101.b7, U4101.58
unnamed: R202.1, U201.54
unnamed: R203.2, U201.38
unnamed: R1001.2, U1001.11
unnamed: TP1601.1, U1601.16
unnamed: TP2001.1, U2001.16
unnamed: TP2401.1, U2401.16
unnamed: TP2801.1, U2801.16
unnamed: TP3201.1, U3201.16
unnamed: TP3601.1, U3601.16
unnamed: TP4001.1, U4001.16

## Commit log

2020-07-18 Some very rough stuff
2020-07-18 Rough block diagram
2020-07-18 Note where the ip2721
2020-08-10 Work so far.
